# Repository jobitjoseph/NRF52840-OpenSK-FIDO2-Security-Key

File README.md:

# Build Your Own FIDO2 Security Key with nRF52840 and OpenSK

An open-source USB FIDO2 security key built around the **Nordic nRF52840** and **Google's OpenSK** firmware.

This project demonstrates how to build a hardware-backed authentication device that can be used with websites and services supporting **FIDO2 / WebAuthn**.

The custom hardware uses the nRF52840's native USB interface and hardware-assisted cryptography to implement the security-key functionality. The device communicates with the host computer over USB and keeps the credential's private key on the security key rather than transferring it to the computer or website.

---

## Features

- FIDO2 / WebAuthn authentication
- nRF52840-based custom hardware
- OpenSK open-source security-key firmware
- USB HID FIDO2 transport
- Hardware-assisted cryptography using the nRF52840
- Credential private key remains on the security key
- USB DFU / UF2 firmware updates
- Custom capacitive touch input for user presence
- RGB LED for status indication
- Custom compact PCB
- Open-source hardware and firmware modifications

---

## How It Works

The security key acts as a FIDO2 authenticator between the browser and the website.

During registration, the security key generates a unique credential key pair:

```text
                 Registration

Website
   │
   │ Registration request
   ▼
Browser
   │
   │ FIDO2 / CTAP2 over USB HID
   ▼
OpenSK on nRF52840
   │
   ├── Generate credential key pair
   │
   ├── Private key ──► Stored on security key
   │
   └── Public key ───► Website

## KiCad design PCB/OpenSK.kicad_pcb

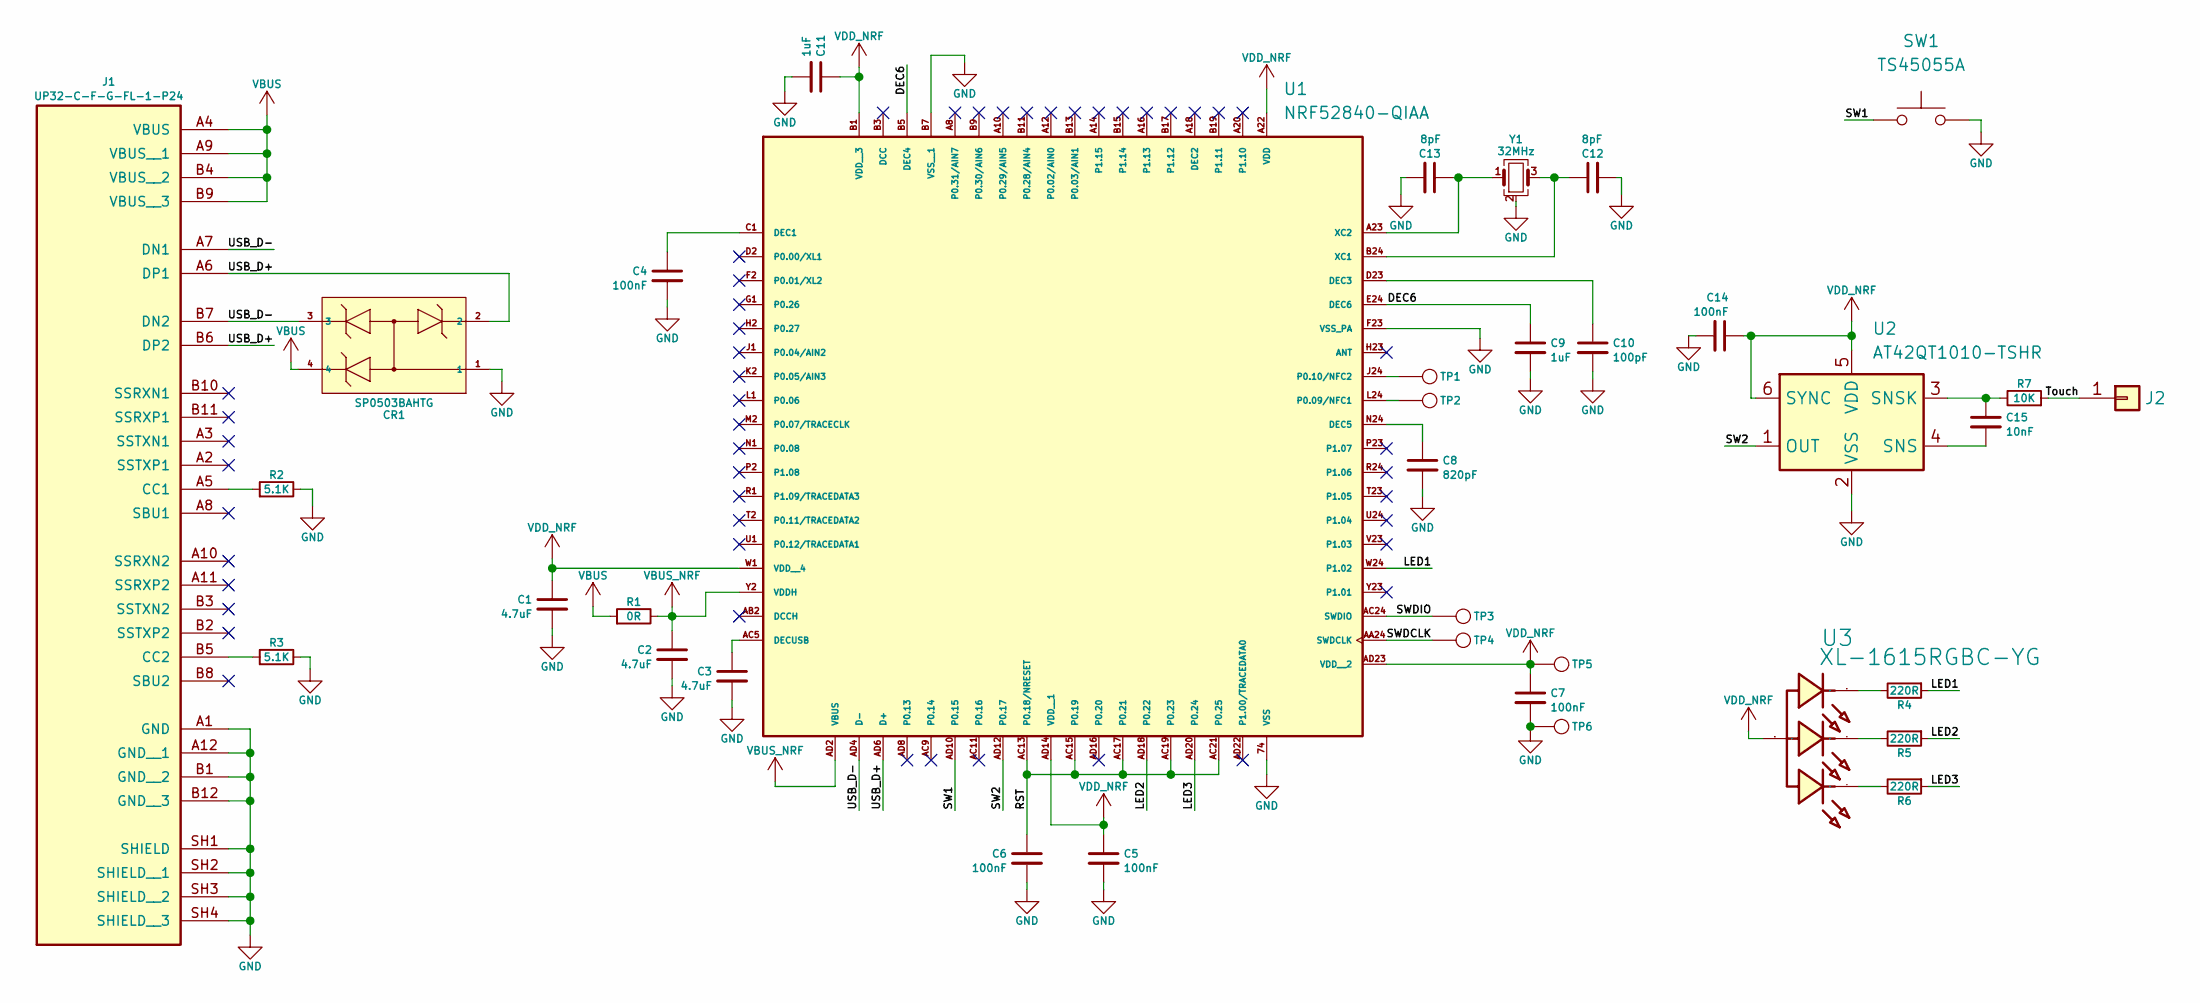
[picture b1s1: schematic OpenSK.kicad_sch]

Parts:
C1, C2, C3: 4.7uF; C_0402_1005Metric; LCSC Part # C1779
C4, C5, C6, C7, C14: 100nF; C_0402_1005Metric; LCSC Part # C14663
C8: 820pF; C_0402_1005Metric; LCSC Part # C1523
C9, C11: 1uF; C_0402_1005Metric; LCSC Part # C52923
C10: 100pF; C_0402_1005Metric; LCSC Part # C1546
C12, C13: 8pF; C_0402_1005Metric; LCSC Part # C32949
C15: 10nF; C_0402_1005Metric; LCSC Part # C1710
CR1: SP0503BAHTG; TVS-SP05_LTF-L; LCSC Part # C7074
J1: UP32-C-F-G-FL-1-P24; SAMESKY_UP32-C-F-G-FL-1-P24; PARTREV 1.01; LCSC Part # C42453853
J2: Conn_01x01; PinHeader_1x01_P2.54mm_Vertical
R1: 0R; R_0402_1005Metric; LCSC Part # C17168
R2, R3: 5.1K; R_0402_1005Metric; LCSC Part # C25905
R4, R5, R6: 220R; R_0402_1005Metric; LCSC Part # C25091
R7: 10K; R_0402_1005Metric; LCSC Part # C25744
SW1: TS45055A; SW-SMD_4P-L4.5-W4.5-P3.50-LS5.0; LCSC Part # C412371
TP1, TP2, TP3, TP4, TP5, TP6: TestPoint; TestPoint_Pad_D1.0mm
U1: NRF52840-QIAA; XCVR_NRF52840-QIAA-R; PARTREV v1.1; LCSC Part # NRF52840-QIAA-R
U2: AT42QT1010-TSHR; SOT-23-6; LCSC Part # C74512
U3: XL-1615RGBC-YG; LED-SMD_4P-L1.6-W1.5-BL-2; Manufacturer Part XL-1615RGBC-YG; LCSC Part # C5440642
Y1: 32MHz; Crystal_SMD_2016-4Pin_2.0x1.6mm; LCSC Part # C383840

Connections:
/DEC6: C9.1, U1.B5 (DEC4), U1.E24 (DEC6)
/LED1: R4.1, U1.W24 (P1.02)
/LED2: R5.1, U1.AD18 (P0.22)
/LED3: R6.1, U1.AD20 (P0.24)
/RST: C6.1, U1.AC13 (P0.18/NRESET), U1.AC15 (P0.19), U1.AC17 (P0.21), U1.AC19 (P0.23), U1.AC21 (P0.25)
/SW1: SW1.2, U1.AD10 (P0.15)
/SW2: U1.AD12 (P0.17), U2.1 (OUT)
/SWDCLK: TP4.1 (1_1), U1.AA24 (SWDCLK)
/SWDIO: TP3.1 (1_1), U1.AC24 (SWDIO)
/Touch: J2.1 (Pin_1_1), R7.1
/USB_D+: CR1.2, J1.A6 (DP1), J1.B6 (DP2), U1.AD6 (D+)
/USB_D-: CR1.3, J1.A7 (DN1), J1.B7 (DN2), U1.AD4 (D-)
GND: C1.2, C2.2, C3.2, C4.2, C5.2, C6.2, C7.2, C8.2, C9.2, C10.2, C11.2, C12.2, C13.2, C14.2, CR1.1, J1.A1 (GND), J1.A12 (GND__1), J1.B1 (GND__2), J1.B12 (GND__3), J1.SH1 (SHIELD), J1.SH2 (SHIELD__1), J1.SH3 (SHIELD__2), J1.SH4 (SHIELD__3), R2.2, R3.2, SW1.1, TP6.1 (1_1), U1.74 (VSS), U1.B7 (VSS__1), U1.F23 (VSS_PA), U2.2 (VSS), Y1.2 (G), Y1.4 (G)
unnamed: J1.A5 (CC1), R2.1
unnamed: J1.B5 (CC2), R3.1
unnamed: R4.2, U3.4 (K)
unnamed: R5.2, U3.3 (K)
unnamed: R6.2, U3.2 (K)
unnamed: C4.1, U1.C1 (DEC1)
unnamed: C10.1, U1.D23 (DEC3)
unnamed: C8.1, U1.N24 (DEC5)
unnamed: C3.1, U1.AC5 (DECUSB)
unnamed: TP2.1 (1_1), U1.L24 (P0.09/NFC1)
unnamed: TP1.1 (1_1), U1.J24 (P0.10/NFC2)
unnamed: C12.1, U1.B24 (XC1), Y1.3
unnamed: C13.1, U1.A23 (XC2), Y1.1
unnamed: C15.2, U2.4 (SNS)
unnamed: C15.1, R7.2, U2.3 (SNSK)
VBUS: CR1.4, J1.A4 (VBUS), J1.A9 (VBUS__1), J1.B4 (VBUS__2), J1.B9 (VBUS__3), R1.1
VBUS_NRF: C2.1, R1.2, U1.AD2 (VBUS), U1.Y2 (VDDH)
VDD_NRF: C1.1, C5.1, C7.1, C11.1, C14.1, TP5.1 (1_1), U1.A22 (VDD), U1.AD14 (VDD__1), U1.AD23 (VDD__2), U1.B1 (VDD__3), U1.W1 (VDD__4), U2.5 (VDD), U2.6 (SYNC), U3.1 (A)

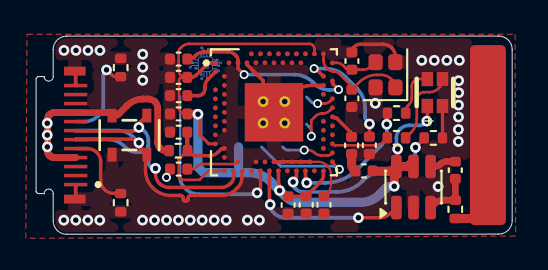
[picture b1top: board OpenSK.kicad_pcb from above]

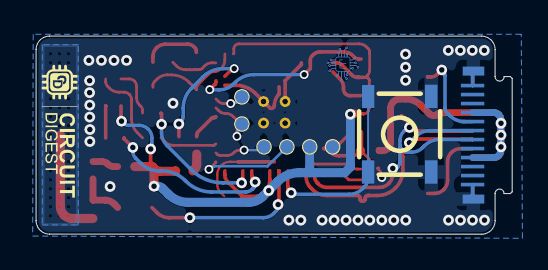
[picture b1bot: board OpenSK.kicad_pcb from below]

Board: 2 copper layers, 26.5 x 11.0 mm, 36 parts (7 on the bottom side), 31 nets.
